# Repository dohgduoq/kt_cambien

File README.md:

# KT Cam Bien

Project phục vụ đọc dữ liệu cảm biến và điều khiển các thiết bị ngoại vi.
Hệ thống sử dụng ESP32 DHT11 và cảm biến độ ẩm đất, hiển thị OLED, điều khiển bơm và quạt bằng nút bấm hoặc giao diện web.

## Cấu trúc project

```text
kt_cambien/
├── kt_cambien.ino
├── src/
│   ├── actuators.cpp
│   ├── comm.cpp
│   ├── display.cpp
│   └── sensors.cpp
├── lib/
│   ├── actuators.h
│   ├── comm.h
│   ├── config.h
│   ├── display.h
│   └── sensors.h
├── .gitignore
└── README.md
```

## Chức năng

- Đọc dữ liệu từ cảm biến.
- Điều khiển thiết bị ngoại vi.
- Giao tiếp và trao đổi dữ liệu.
- Hiển thị thông tin qua giao diện hiển thị.

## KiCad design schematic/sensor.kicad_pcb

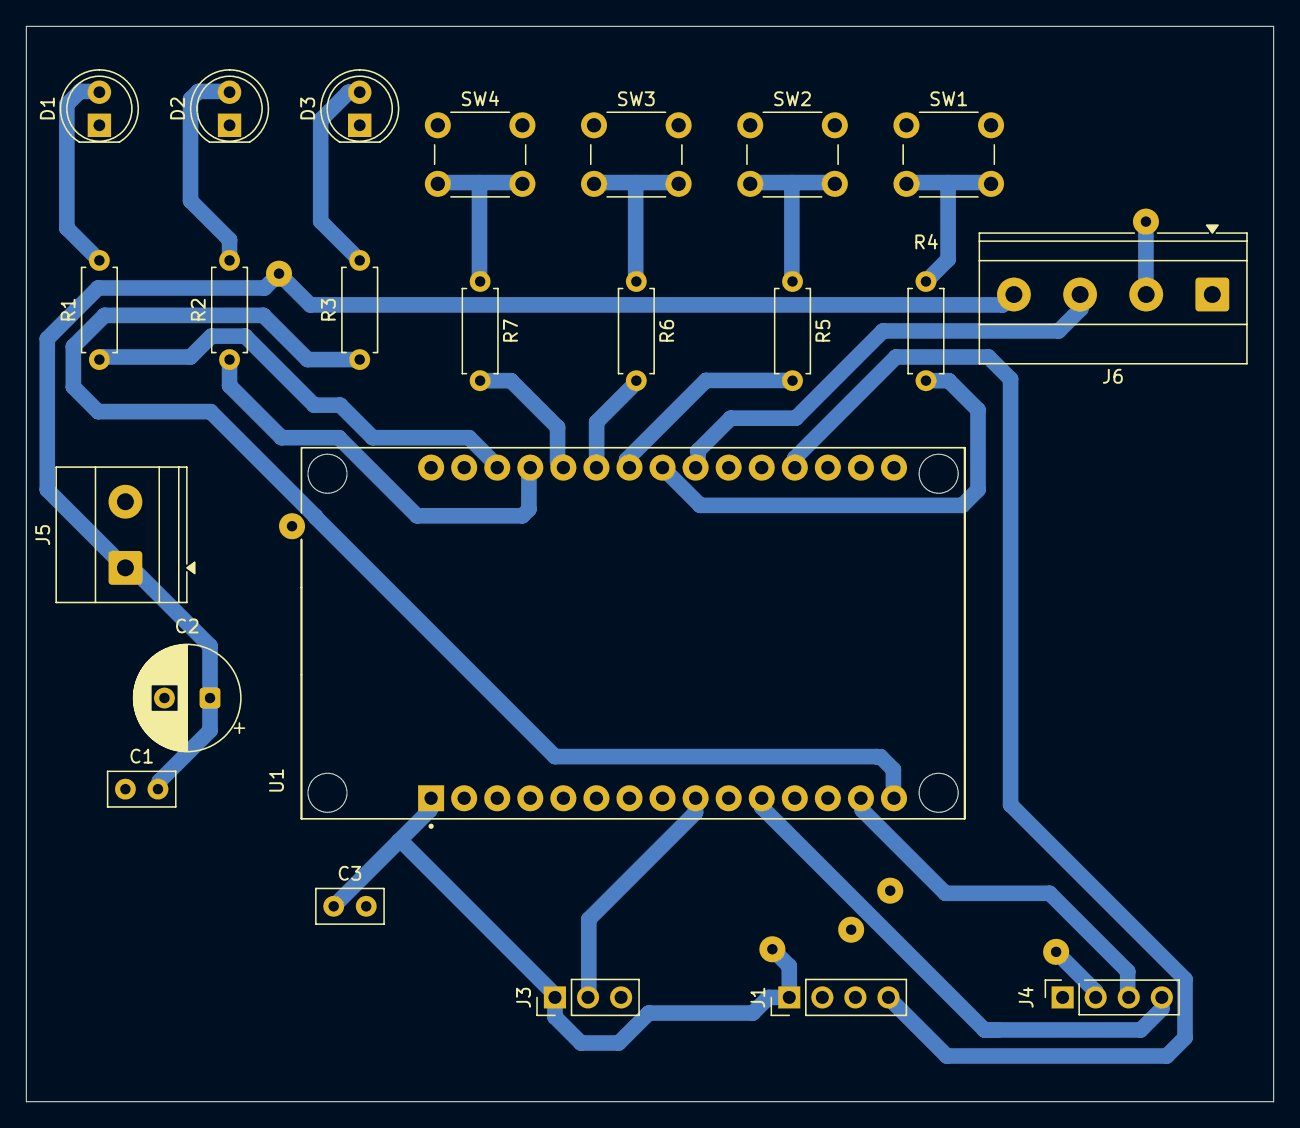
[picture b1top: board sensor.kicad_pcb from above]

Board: 2 copper layers, 95.8 x 82.6 mm, 28 parts (0 on the bottom side), 23 nets.

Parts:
C1, C3: 100nF; C_Disc_D5.0mm_W2.5mm_P2.50mm
C2: 220uF; CP_Radial_D8.0mm_P3.50mm
D1: Connect; LED_D5.0mm
D2: Trang_Thai; LED_D5.0mm
D3: WIFI; LED_D5.0mm
J1: SOIL_LM393; PinHeader_1x04_P2.54mm_Vertical
J3: DHT11; PinHeader_1x03_P2.54mm_Vertical
J4: OLED_I2C; PinSocket_1x04_P2.54mm_Vertical
J5: Screw_Terminal_01x02; TerminalBlock_Phoenix_MKDS-1,5-2-5.08_1x02_P5.08mm_Horizont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
J6: Relay 2 Kênh; TerminalBlock_Phoenix_MKDS-1,5-4-5.08_1x04_P5.08mm_Horizont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
JP1: WIRE_+3V3; JP1_Wire
JP2: WIRE_VBUS; JP2_Wire
JP3: WIRE_IN1; JP3_Wire
JP4: WIRE_GND; JP4_Wire
JP5: WIRE_GND; JP5_Wire
R1, R2, R3: 330; R_Axial_DIN0207_L6.3mm_D2.5mm_P7.62mm_Horizontal
R4, R5, R6, R7: 100; R_Axial_DIN0207_L6.3mm_D2.5mm_P7.62mm_Horizontal
SW1: TRAI; SW_PUSH_6mm
SW2: PHAI; SW_PUSH_6mm
SW3: MODE; SW_PUSH_6mm
SW4: OK; SW_PUSH_6mm
U1: ESP32-DEVKIT-V1; MODULE_ESP32_DEVKIT_V1

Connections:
+3V3: C3.1, J1.1, J3.1, J4.2, JP1.1, U1.1 (3V3)
A0: J1.4, U1.19 (D34)
DATA: J3.2, U1.9 (D18)
GND: C1.1, C2.2, C3.2, D1.1 (K), D2.1 (K), D3.1 (K), J1.2, J3.3, J4.1, J5.2, J6.1, JP4.1, JP5.1, SW1.1, SW2.1, SW3.1, SW4.1, U1.2 (GND), U1.29 (GND)
IN1: J6.2, JP3.1, U1.21 (D32)
IN2: J6.3, U1.22 (D33)
LED1: D1.2 (A), R1.2
LED2: D2.2 (A), R2.2
LED3: D3.2 (A), R3.2
unnamed: R2.1, U1.27 (D12)
unnamed: R1.1, U1.28 (D13)
unnamed: R7.2, U1.26 (D14)
unnamed: R3.1, U1.15 (D23)
unnamed: R4.2, U1.23 (D25)
unnamed: R5.2, U1.24 (D26)
unnamed: R6.2, U1.25 (D27)
SCL: J4.3, U1.14 (D22)
SDA: J4.4, U1.11 (D21)
SW1: R4.1, SW1.2
SW2: R5.1, SW2.2
SW3: R6.1, SW3.2
SW4: R7.1, SW4.2
VBUS: C1.2, C2.1, J5.1, J6.4, JP2.1, U1.30 (VIN)

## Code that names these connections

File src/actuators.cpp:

#include "../lib/actuators.h"

struct Button {
  uint8_t pin;
  bool lastStableState;
  bool lastReading;
  unsigned long lastDebounceTime;
};

static Button btnPump = {PIN_SW1, HIGH, HIGH, 0}; 
static Button btnFan  = {PIN_SW2, HIGH, HIGH, 0}; 
static Button btnMode = {PIN_SW3, HIGH, HIGH, 0}; 
static Button btnPage = {PIN_SW4, HIGH, HIGH, 0}; 

static constexpr unsigned long BUTTON_DEBOUNCE_MS = 30;
static bool checkButtonPressed(Button &btn, const char* btnName) {
  bool pressed = false;
  int reading = digitalRead(btn.pin);

  if (reading != btn.lastReading) {
    btn.lastDebounceTime = millis();
    btn.lastReading = reading;
    
  }

  if ((millis() - btn.lastDebounceTime) >= BUTTON_DEBOUNCE_MS) {
    if (reading != btn.lastStableState) {
      btn.lastStableState = reading;
      if (btn.lastStableState == LOW) {
        pressed = true;
      }
    }
  }
  return pressed;
}

void initActuators() {
  
  pinMode(PIN_SW1, INPUT_PULLUP);
  pinMode(PIN_SW2, INPUT_PULLUP);
  pinMode(PIN_SW3, INPUT_PULLUP);
  pinMode(PIN_SW4, INPUT_PULLUP);

  digitalWrite(PIN_RELAY_PUMP, RELAY_OFF);
  digitalWrite(PIN_RELAY_FAN, RELAY_OFF);
  pinMode(PIN_RELAY_PUMP, OUTPUT);
  pinMode(PIN_RELAY_FAN, OUTPUT);

  pinMode(PIN_LED1, OUTPUT);
  pinMode(PIN_LED2, OUTPUT);
  pinMode(PIN_LED3, OUTPUT);
  digitalWrite(PIN_LED1, HIGH); 
  digitalWrite(PIN_LED2, LOW);
  digitalWrite(PIN_LED3, LOW);

  const uint8_t ledPins[] = {PIN_LED1, PIN_LED2, PIN_LED3};
  for (uint8_t pin : ledPins) digitalWrite(pin, LOW);
  for (uint8_t pin : ledPins) {
    
    digitalWrite(pin, HIGH);
    delay(250);
    digitalWrite(pin, LOW);
  }
  digitalWrite(PIN_LED1, HIGH);
  
}

void applyRelays(bool pumpState, bool fanState) {
  digitalWrite(PIN_RELAY_PUMP, pumpState ? RELAY_ON : RELAY_OFF);
  digitalWrite(PIN_RELAY_FAN,  fanState  ? RELAY_ON : RELAY_OFF);
}

void updateLeds(SystemMode mode, bool wifiConnected) {
  
  digitalWrite(PIN_LED1, HIGH);

  static unsigned long lastBlinkMode = 0;
  static bool led2State = false;
  if (mode == MODE_AUTO) {
    digitalWrite(PIN_LED2, HIGH);
  } else {
    if (millis() - lastBlinkMode >= 500) {
      lastBlinkMode = millis();
      led2State = !led2State;
      digitalWrite(PIN_LED2, led2State ? HIGH : LOW);
    }
  }

  static unsigned long lastBlinkWifi = 0;
  static bool led3State = false;
  if (wifiConnected) {
    digitalWrite(PIN_LED3, HIGH);
  } else {
    if (millis() - lastBlinkWifi >= 250) {
      lastBlinkWifi = millis();
      led3State = !led3State;
      digitalWrite(PIN_LED3, led3State ? HIGH : LOW);
    }
  }
}

void processControlLogic() {
  
  static bool sw1Pressed = false, sw2Pressed = false;
  static bool sw3Pressed = false, sw4Pressed = false;
  sw1Pressed |= checkButtonPressed(btnPump, "SW1 (Pump)");
  sw2Pressed |= checkButtonPressed(btnFan,  "SW2 (Fan)");
  sw3Pressed |= checkButtonPressed(btnMode, "SW3 (Mode)");
  sw4Pressed |= checkButtonPressed(btnPage, "SW4 (OLED)");

  if (xSemaphoreTake(g_dataMutex, pdMS_TO_TICKS(20)) == pdTRUE) {
    
    if (sw3Pressed) {
      g_data.mode = (g_data.mode == MODE_AUTO) ? MODE_MANUAL : MODE_AUTO;
      
    }

    if (sw4Pressed) {
      g_data.displayPage = (g_data.displayPage == 0) ? 1 : 0;
      
    }

    if (sw1Pressed) {
      if (g_data.mode == MODE_AUTO) {
        g_data.mode = MODE_MANUAL;
        
      }
      g_data.relayPump = !g_data.relayPump;
      
    }

    if (sw2Pressed) {
      if (g_data.mode == MODE_AUTO) {
        g_data.mode = MODE_MANUAL;
        
      }
      g_data.relayFan = !g_data.relayFan;
      
    }

    if (g_data.mode == MODE_AUTO) {
      
      if (g_data.soilMoisture < SOIL_DRY_THRESHOLD) {
        g_data.relayPump = true;  
      } else if (g_data.soilMoisture > (SOIL_DRY_THRESHOLD + SOIL_HYSTERESIS)) {
        g_data.relayPump = false; 
      }

      if (g_data.dhtValid && g_data.temperature > TEMP_HIGH_THRESHOLD) {
        g_data.relayFan = true;   
      } else if (g_data.dhtValid && g_data.temperature < (TEMP_HIGH_THRESHOLD - TEMP_HYSTERESIS)) {
        g_data.relayFan = false;  
      }
    }

    applyRelays(g_data.relayPump, g_data.relayFan);

    updateLeds(g_data.mode, g_data.wifiConnected);

    sw1Pressed = sw2Pressed = sw3Pressed = sw4Pressed = false;
    xSemaphoreGive(g_dataMutex);
  }
}
